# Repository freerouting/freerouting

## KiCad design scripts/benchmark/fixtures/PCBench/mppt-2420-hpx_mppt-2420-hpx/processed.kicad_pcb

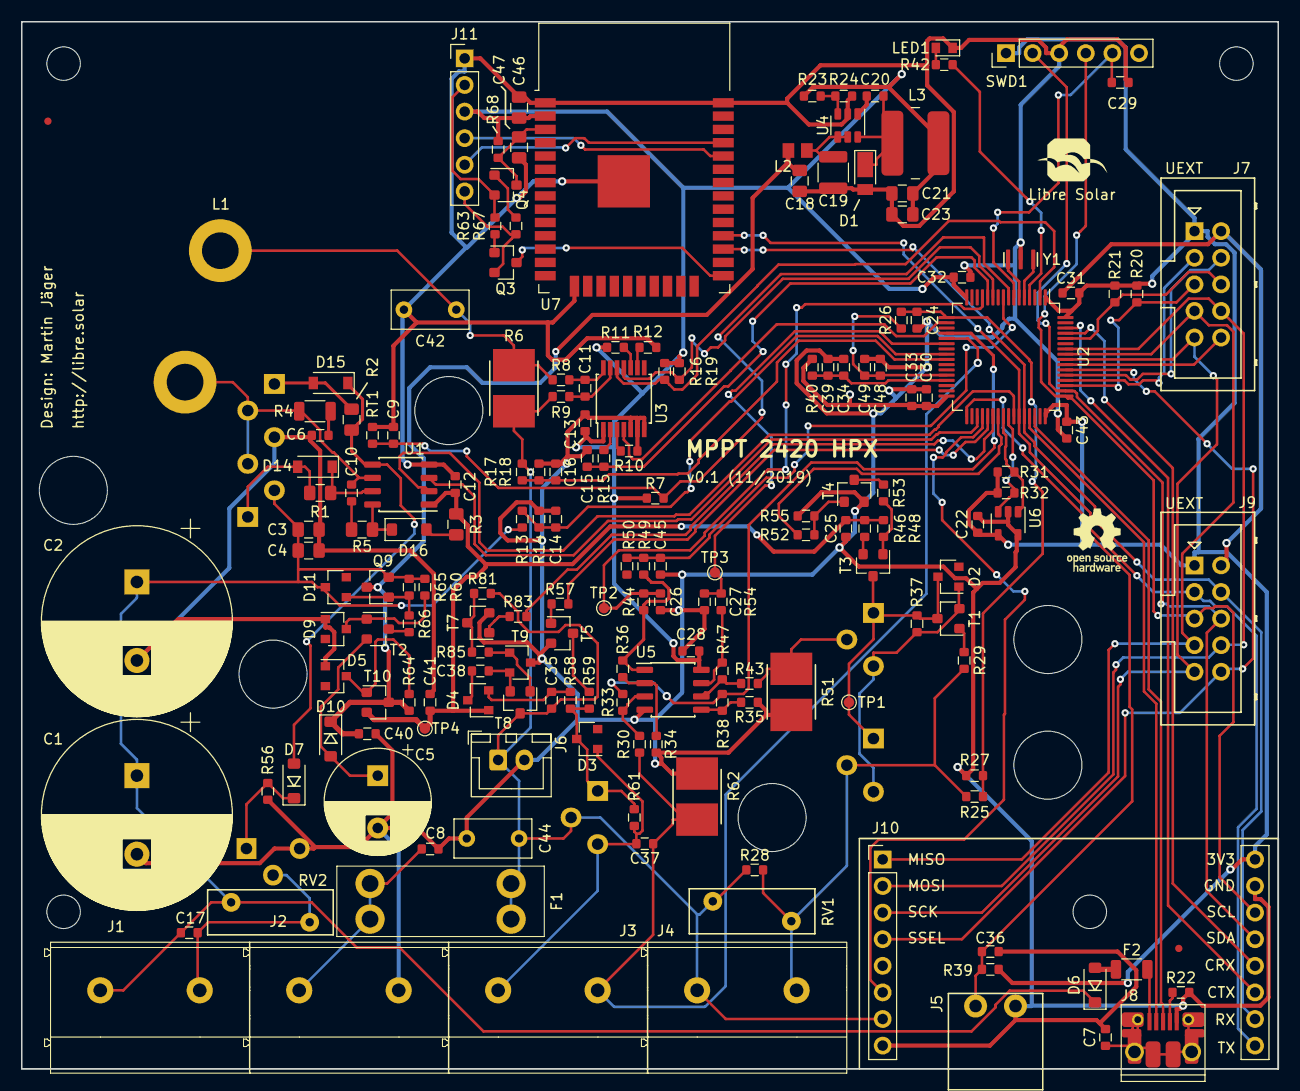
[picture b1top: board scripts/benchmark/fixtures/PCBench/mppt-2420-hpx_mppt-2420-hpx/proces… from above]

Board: 4 copper layers, 120.0 x 100.0 mm, 191 parts (0 on the bottom side), 116 nets.

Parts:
C1, C2: 560µF; CP_Radial_D18.0mm_P7.50mm
C3, C18: 1µF; C_0805_2012
C4: 100nF; C_0805_2012
C5: 820µF; CP_Radial_D10.0mm_P5.00mm
C6: 1nF; C_0603_1608
C7, C8, C14, C16, C17, C24, C26, C27, C34, C37, C38, C45: 10nF; C_0603_1608
C9, C10, C13, C15, C20, C22, C25, C28, C29, C30, C31, C32, C35, C36, C43, C48: 100nF; C_0603_1608
C11: 100pF; C_0603_1608
C12, C33, C39, C49: 2.2µF; C_0603_1608
C19: 4.7µF; C_1210_3225
C21, C23, C46: 10µF; C_0805_2012
C40: 1µF; C_0603_1608
C41: 4.7µF; C_0603_1608
C42, C44: 0.22µF; C_Rect_L7.2mm_W3.5mm_P5.00mm_FKS2_FKP2_MKS2_MKP2
C47: 2.2µF; C_0805_2012
D1: SS16FP; D_PowerDI-123
D2, D3, D5, D9, D11: 12V; D_SOT-23_ANK
D4: BAT54S; SOT-23
D6, D10, D16: 1N4148; D_SOD-123
D7, D14, D15: SS14FL; D_SOD-123
F1: 25A; Keystone-Fuse-3557-2
F2: 200mA; R_1206_3216
FID1, FID2: Fiducial; Fiducial_0.7mm
J1, J2, J3, J4: MKDS 5/ 2-9,5; Phoenix_Contact_MKDS_5-2-9,5
J5: Phoenix Contact MC 1,5; Phoenix_Contact_MC_1,5_2-G-3,81
J6: JST XH; JST_XH_B2B-XH-A_1x02_P2.50mm_Vertical
J7, J9: UEXT; Box_Header_2x05x2.54mm_Straight
J8: USB Micro B; USB_Micro-B_10103594-0001LF
J10: CommsExt_2x8
J11: Conn_01x06; PinHeader_1x06_P2.54mm_Vertical
L1: 33µH; L-FERYSTER-DTMSS-27
L2: 4.7µH; L_0805_2012Metric
L3: 47µH; Bourns_SRN6045TA
LED1: red; LED_0603_1608Metric
LOGO1: LIBRE_SOLAR; LIBRESOLAR_LOGO
LOGO2: OPEN_HARDWARE; OSHW-Logo_5.7x6mm_SilkScreen
MK1, MK2, MK3, MK4: Mounting_Hole; MountingHole_3.2mm_M3
Q1, Q2, Q5, Q6, Q7, Q8: IPA045N10N3G; TO-220-3_Horizontal_BottomHeatsink
Q3, Q4: MMBT3904; SOT-23
Q9: DMP10H4D2S; SOT-23
R1, R2, R3, R5: 3R3; R_0805_2012
R4: 2R2; R_1206_3216
R6, R51, R62: 2m; R_Bourns_CRE2512
R7, R14, R16, R19, R24, R39, R59, R63, R67, R68, R83: 10k; R_0603_1608
R8, R9: 10R; R_0603_1608
R10, R12, R15: ?; R_0603_1608
R11, R13, R17, R22, R58, R81: 100k; R_0603_1608
R18: 5.6k; R_0603_1608
R20, R21, R30, R31, R32, R34, R35, R43, R52, R54, R57: 2.2k; R_0603_1608
R23: 33k; R_0603_1608
R25, R29, R48, R53, R55: 120k; C_0603_1608
R26, R50: 8.2k; C_0603_1608
R27, R49: 12k; C_0603_1608
R28, R60, R64, R65, R66: 12k; R_0603_1608
R33, R36, R38, R47: 68k; C_0603_1608
R37: 39k; R_0603_1608
R40: 100R; R_0603_1608
R42, R46: 470R; R_0603_1608
R44: 2.2k; C_0603_1608
R56, R61: 1M; R_0603_1608
R85: 1k; R_0603_1608
RT1: 10k; R_0603_1608
RV1, RV2: 56V; RV_Disc_D12mm_W4.3mm_P7.5mm
SWD1: ST_Nucleo_SWD; PinHeader_1x06_P2.54mm_Vertical
T1, T2, T4, T5, T7, T8, T10: MMBT3904; SOT-23
T3, T9: MMBT3906; SOT-23
TEST: TestPoint_Pad_1.0x1.0mm
TP1: G_PWM; TestPoint_Pad_D1.0mm
TP2: I_LOAD; TestPoint_Pad_D1.0mm
TP3: I_SOLAR; TestPoint_Pad_D1.0mm
TP4: 12V; TestPoint_Pad_D1.0mm
U1: LM5107; SOIC-8_3.9x4.9mm_Pitch1.27mm
U2: STM32G431RBTx; LQFP-64_10x10mm_P0.5mm
U3: INA303A1; TSSOP-14_4.4x5mm_P0.65mm
U4: LMR16006X; SOT-23-6
U5: TLV9002; SOIC-8_3.9x4.9mm_Pitch1.27mm
U6: 24AA01; SOT-23-5
U7: ESP32-WROOM-32D; ESP32-WROOM-32
Y1: 8MHz; Resonator_Murata_CSTNE

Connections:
+3V3: C13.2, C21.1, C22.1, C23.1, C28.1, C30.1, C31.1, C32.1, C33.1, C43.1, C46.1, J7.1, J9.1, J10.16, J11.3, L3.2, R7.1, R11.2, R16.2, R19.2, R20.2, R21.2, R23.1, R31.2, R32.2, R39.1, R40.2, R68.2, SWD1.1, U2.1, U2.16, U2.32, U2.48, U2.64, U3.1, U5.8, U6.4, U7.2
+12V: C12.1, C25.1, C41.1, D4.1, R3.2, R46.1, R48.2, T10.2, TP4.1, U1.1
/Accessories/CAN_RX: J10.12, U2.61
/Accessories/CAN_TX: J10.11, U2.62
/Accessories/COM_I2C_SCL: J9.5, J10.14, SWD1.4, U2.49
/Accessories/COM_I2C_SDA: J9.6, J10.13, SWD1.2, U2.50
/Accessories/COM_MISO: J7.7, J9.7, J10.1, U2.57
/Accessories/COM_MOSI: J7.8, J9.8, J10.2, U2.58
/Accessories/COM_PWRI: J10.6, U2.36
/Accessories/COM_RX: J9.4, J10.10, U2.44, U7.27
/Accessories/COM_SCK: J7.9, J9.9, J10.3, U2.56
/Accessories/COM_SSEL: J9.10, J10.4, U2.54
/Accessories/COM_TX: J9.3, J10.9, U2.43, U7.28
/Accessories/DTR: J11.6, Q3.2, R67.2
/Accessories/FTDI_RX: J11.5, U7.35
/Accessories/FTDI_TX: J11.4, U7.34
/Accessories/GPIO0: Q3.3, U7.25
/Accessories/RESET: C47.1, Q4.3, R68.1, U7.3
/Accessories/RTS: J11.2, Q4.2, R63.2
/BAT+: C8.1, F1.2, J2.1
/DC/DC/HS_DRV: D14.1, R1.2, U1.7
/DC/DC/LS_DRV: D7.2, D15.1, R2.2, U1.5
/DC/DC/NOC_ALERT: R19.1, U2.11, U3.11
/DC/DC/POC_ALERT: R16.1, U2.2, U3.12
/DC/DC/PWM_HS: U1.2, U2.42
/DC/DC/PWM_LS: U1.3, U2.35
/DC/DC/SHUNT+: C42.1, L1.2, R6.2, R8.1
/DC/DC/SW_NODE: C10.2, L1.1, Q1.3, Q2.2, R4.2, U1.6
/DCDC_HV+: C1.1, C2.1, C3.1, C4.1, C17.1, D6.1, D11.1, J1.1, Q1.2, Q9.2, R13.1, R60.2, R65.2, RV2.1
/DCDC_HV-: C17.2, J1.2, Q8.2, RV2.2
/LOAD+: C37.1, D3.2, J3.1, Q7.3, R61.2
/LOAD-: C37.2, J3.2, R30.2, R62.1, U2.21
/LV switches/CP_OUT: C35.1, D4.2, R58.1
/LV switches/CP_PWM: R83.2, U2.38
/LV switches/CP_SW: C38.2, T8.2, T9.2
/LV switches/G_PWM: D2.1, Q5.1, Q6.1, R37.1, T1.3, T3.3, TP1.1
/LV switches/PWM_SW_EN: R52.2, U2.39
/LV switches/S_SHUNT-: Q6.2, R43.2, R51.1
/MCU/ADC1_IN4: C24.1, R25.2, R26.2, R27.1, U2.17
/MCU/ADC1_IN6: C9.1, R7.2, RT1.1, U2.8
/MCU/ADC1_IN12: C16.1, R17.2, R18.1, U2.25
/MCU/ADC1_IN15: C14.1, R13.2, R14.1, U2.24
/MCU/ADC2_IN5: C27.1, R54.2, TP3.1, U2.22
/MCU/ADC12_IN1: C15.1, R15.2, U2.12
/MCU/ADC12_IN2: C26.1, R44.2, TP2.1, U2.13
/MCU/COMP3_INP: C45.1, R49.1, R50.2, U2.9
/MCU/DAC1: U2.18, U3.4
/MCU/DAC2: R33.1, R38.2, U2.20
/MCU/GPIOB_15: R57.1, U2.37
/MCU/GPIOD_PD2: J7.10, U2.55
/MCU/I2C1_SCL: J7.5, R20.1, U2.51
/MCU/I2C1_SDA: J7.6, R21.1, U2.60
/MCU/I2C3_SCL: R31.1, U2.40, U6.1
/MCU/I2C3_SDA: R32.1, U2.41, U6.3
/MCU/LED_PWR: R42.2, U2.4
/MCU/OSC_IN: U2.5, Y1.3
/MCU/OSC_OUT: U2.6, Y1.1
/MCU/TEMP_BAT: C36.1, J5.1, R39.2, U2.33
/MCU/USART3_RX: J7.4, U2.53
/MCU/USART3_TX: J7.3, U2.52
/MCU/USB_DM: J8.2, U2.45
/MCU/USB_DP: J8.3, U2.46
/MCU/~RESET: C29.1, SWD1.5, U2.7
/PWM_SW-: J4.2, Q5.2, R25.1, R28.2, R29.2, RV1.2
/Power Supply/SMPS_SUPPLY: C18.1, C40.1, D10.1, L2.1, Q9.3, R64.2, T10.3
GND: C1.2, C2.2, C3.2, C4.2, C5.2, C6.2, C7.2, C8.2, C9.2, C12.2, C13.1, C14.2, C15.2, C16.2, C18.2, C19.2, C21.2, C22.2, C23.2, C24.2, C25.2, C26.2, C27.2, C28.2, C29.2, C30.2, C31.2, C32.2, C33.2, C34.2, C36.2, C39.2, C40.2, C41.2, C42.2, C43.2, C44.1, C45.2, C46.2, C47.2, C48.2, C49.2, D1.2, D5.2, D9.2, J2.2, J5.2, J6.2, J7.2, J8.5, J9.2, J10.8, J10.15, J11.1, LED1.1, Q2.3, Q8.3, R10.1, R12.1, R14.2, R18.2, R22.2, R24.2, R27.2, R34.2, R35.2, R51.2, R55.2, R56.2, R62.2, RT1.2, SWD1.3, T4.2, T5.2, T7.2, T9.3, U1.4, U3.5, U3.6, U3.7, U4.2, U5.4, U6.2, U6.5, U7.1, U7.15, U7.38, U7.39, Y1.2
unnamed: C6.1, R4.1
unnamed: C7.1, J8.6
unnamed: C10.1, R5.2
unnamed: C11.1, R8.2, U3.14
unnamed: C11.2, R9.2, U3.13
unnamed: C19.1, L2.2, U4.4, U4.5
unnamed: C20.1, U4.1
unnamed: C20.2, D1.1, L3.1, U4.6
unnamed: C38.1, D4.3
unnamed: D2.2, Q5.3, Q6.3, R37.2, T1.2
unnamed: D3.1, Q7.1, R58.2, R59.2, R61.1
unnamed: D5.1, R64.1, T10.1
unnamed: D6.2, F2.1
unnamed: D7.1, Q8.1, R56.1
unnamed: D9.1, R60.1, T2.1
unnamed: D11.2, Q9.1, R65.1, R66.2
unnamed: D14.2, Q1.1, R1.1
unnamed: D15.2, Q2.1, R2.1
unnamed: D16.1, R5.1, U1.8
unnamed: D16.2, R3.1
unnamed: F2.2, J8.1
unnamed: J8.4, R22.1
unnamed: LED1.2, R42.1
unnamed: Q3.1, R63.1
unnamed: Q4.1, R67.1
unnamed: R10.2, U3.3
unnamed: R11.1, U3.10
unnamed: R12.2, U3.9
unnamed: R15.1, U3.2
unnamed: R23.2, R24.1, U4.3
unnamed: R29.1, T1.1
unnamed: R30.1, R33.2, U5.3
unnamed: R34.1, R36.1, U5.2
unnamed: R35.1, R38.1, U5.5
unnamed: R36.2, R44.1, R49.2, U5.1
unnamed: R43.1, R47.1, U5.6
unnamed: R46.2, T3.2
unnamed: R47.2, R54.1, U5.7
unnamed: R48.1, R53.2, T3.1
unnamed: R52.1, R55.1, T4.1
unnamed: R53.1, T4.3
unnamed: R57.2, T5.1
unnamed: R59.1, T5.3
unnamed: R66.1, T2.3
unnamed: R81.1, R85.1, T7.3
unnamed: R83.1, T7.1
unnamed: R85.2, T8.1, T9.1
VBUS: C5.1, C35.2, C44.2, D10.2, F1.1, J4.1, J6.1, J10.7, Q7.2, R6.1, R9.1, R17.1, R28.1, R81.2, RV1.1, T2.2, T8.3
VDDA: C34.1, C39.1, R40.1, U2.29
VREF: C48.1, C49.1, R26.1, U2.28

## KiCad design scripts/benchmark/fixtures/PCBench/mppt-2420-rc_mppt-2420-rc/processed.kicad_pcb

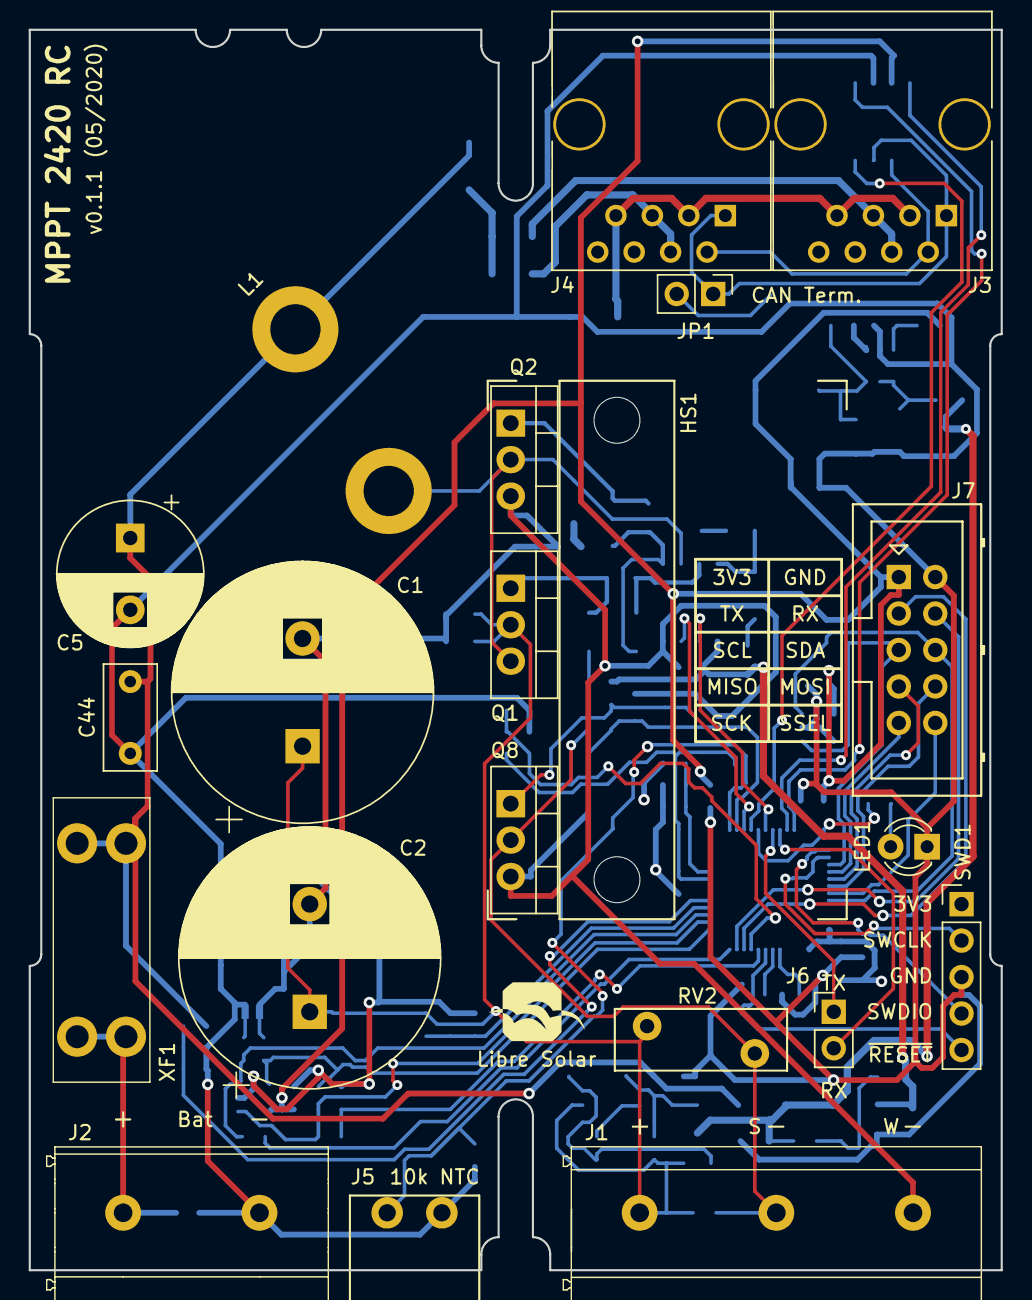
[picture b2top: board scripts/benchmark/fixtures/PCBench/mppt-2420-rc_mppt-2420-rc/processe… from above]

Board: 4 copper layers, 67.7 x 86.4 mm, 120 parts (0 on the bottom side), 71 nets.

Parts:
C1, C2: 560µF; CP_Radial_D18.0mm_P7.50mm
C3, C18, C40: 1µF; C_0805_2012
C4: 100nF; C_0805_2012
C5: 820µF; CP_Radial_D10.0mm_P5.00mm
C6, C15: 1nF; C_0603_1608
C7, C9, C10, C11, C20, C22, C29, C30, C31, C32, C36, C48: 100nF; C_0603_1608
C8, C14, C16, C17, C34: 10nF; C_0603_1608
C12, C33, C39, C41, C49: 2.2µF; C_0603_1608
C19: 4.7µF; C_1210_3225
C21, C23: 10µF; C_0805_2012
C44: 0.22µF; C_Rect_L7.2mm_W3.5mm_P5.00mm_FKS2_FKP2_MKS2_MKP2
D1: SS16FP; D_PowerDI-123
D2, D3: NRVTS260ESFT1G; D_SOD-123
D5, D9, D11: 12V; D_SOT-23_ANK
D7, D14, D15: SS14FL; D_SOD-123
D8: 2.5V; D_SOD-123
D10, D16: 1N4148; D_SOD-123
F1: 25A; NULL
F2, F3: 600mA; Fuse_1206_3216Metric
FID1, FID2: Fiducial; Fiducial_0.7mm
HS1: Heatsink; Fischer_Elektronik_SK573_37,5
J1: MKDS 5/ 3-9,5; Phoenix_Contact_MKDS_5-3-9,5
J2: MKDS 5/ 2-9,5; Phoenix_Contact_MKDS_5-2-9,5
J3, J4: 8P8C; RJ45_8P8C
J5: Phoenix Contact MC 1,5; Phoenix_Contact_MC_1,5_2-G-3,81
J6: Conn_01x02; PinHeader_1x02_P2.54mm_Vertical
J7: UEXT; Box_Header_2x05x2.54mm_Straight
JP1: Jumper_NC_Small; PinHeader_1x02_P2.54mm_Vertical
L1: 33µH; L-FERYSTER-DTMSS-27
L2: 4.7µH; L_0805_2012Metric
L3: 47µH; Bourns_SRN6045TA
LED1: red; LED_D3.0mm
LOGO1: LIBRE_SOLAR; LIBRESOLAR_LOGO
LOGO2: OPEN_HARDWARE; OSHW-Logo_5.7x6mm_SilkScreen
NT1, NT2: Net-Tie_2; NetTie-2_SMD_Pad0.5mm
Q1, Q2, Q8: IPP045N10N3G; TO-220-3_Vertical
Q9: DMP10H4D2S; SOT-23
R1, R2, R3, R5: 3R3; R_0805_2012
R4: 2R2; R_1206_3216
R6: 2m; R_Bourns_CRE2512
R7, R24, R39, R41, R45, R64, R65, R66: 10k; R_0603_1608
R8, R10, R14, R20, R21: 2.2k; R_0603_1608
R9, R11: 68k; R_0603_1608
R12: 0R; R_0603_1608
R13, R17: 100k; R_0603_1608
R15, R42: 1k; R_0603_1608
R18: 5.6k; R_0603_1608
R22: 120R; R_1206_3216
R23, R60: 33k; R_0603_1608
R40: 100R; R_0603_1608
R56: 1M; R_0603_1608
RT1: 10k; R_0603_1608
RV2: 82V; RV_Disc_D12mm_W4.3mm_P7.5mm
SWD1: ST_Nucleo_SWD; PinHeader_1x05_P2.54mm_Vertical
T2, T6, T10: MMBT3904; SOT-23
TP4: 12V; TestPoint_Pad_D1.0mm
U1: LM5107; SOIC-8_3.9x4.9mm_Pitch1.27mm
U2: STM32G431CBTx; LQFP-48_7x7mm_P0.5mm
U3: TLV9001; SOT-23-5
U4: LMR16006X; SOT-23-6
U5: TCAN334; SOIC-8_3.9x4.9mm_Pitch1.27mm
U6: 24AA32; SOT-23-5
XF1: ATO blade fuse; Keystone-Fuse-3557-2
Y1: 8MHz; Resonator_Murata_CSTNE

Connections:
+3V3: C7.1, C11.1, C21.1, C22.1, C23.1, C30.1, C31.1, C32.1, C33.1, J7.1, L3.2, R20.2, R21.2, R23.1, R40.2, SWD1.1, U2.1, U2.48, U3.5, U5.3, U6.4
+12V: C12.1, C41.1, R3.2, R12.1, T10.2, TP4.1, U1.1
/BAT+: C8.1, J2.1, XF1.2
/CAN bus/CAN_GND: D3.2, J3.3, J3.7, J4.3, J4.7
/CAN bus/CAN_H: J3.1, J4.1, JP1.1, U5.7
/CAN bus/CAN_L: J3.2, J4.2, R22.2, U5.6
/CAN bus/CAN_RX: U2.33, U5.4
/CAN bus/CAN_STB: U2.28, U5.8
/CAN bus/CAN_TX: U2.34, U5.1
/CAN bus/CAN_V+1: F2.1, J3.4, J3.5
/CAN bus/CAN_V+2: F3.1, J4.4, J4.5
/DC/DC/HS_DRV: D14.1, R1.2, U1.7
/DC/DC/LS_DRV: D7.2, D15.1, R2.2, U1.5
/DC/DC/PWM_HS: U1.2, U2.30
/DC/DC/PWM_LS: U1.3, U2.27
/DC/DC/SHUNT_N: NT1.2, R10.1
/DC/DC/SHUNT_P: NT2.2, R8.1
/DC/DC/SW_NODE: C10.2, L1.1, Q1.3, Q2.2, R4.2, U1.6
/DCDC_HV+: C1.1, C2.1, C3.1, C4.1, C17.1, D11.1, J1.1, Q1.2, Q9.2, R13.1, R60.2, R65.2, RV2.1
/DCDC_HV-: C17.2, J1.2, Q8.2, R41.1, RV2.2
/MCU/ADC1_IN2: C9.1, R7.2, RT1.1, U2.9
/MCU/ADC1_IN11: D8.1, R41.2, T6.1, U2.26
/MCU/ADC1_IN12: C16.1, R17.2, R18.1, U2.17
/MCU/ADC1_IN15: C14.1, R13.2, R14.1, U2.16
/MCU/ADC2_IN1: C15.1, R15.2, U2.8
/MCU/DAC1: R9.1, U2.12
/MCU/I2C1_SCL: J7.5, R20.1, U2.39, U6.1
/MCU/I2C1_SDA: J7.6, R21.1, U2.44, U6.3
/MCU/LED_PWR: R42.2, U2.29
/MCU/OPAMP2_VINM: R10.2, R11.1, U2.13, U3.4
/MCU/OPAMP2_VINP: R8.2, R9.2, U2.15, U3.3
/MCU/OPAMP2_VOUT: R11.2, R15.1, U2.14, U3.1
/MCU/OSC_IN: U2.5, Y1.3
/MCU/OSC_OUT: U2.6, Y1.1
/MCU/SPI1_MISO: J7.7, U2.41
/MCU/SPI1_MOSI: J7.8, U2.42
/MCU/SPI1_SCK: J7.9, U2.40
/MCU/SPI1_SSEL: J7.10, U2.43
/MCU/SWCLK: SWD1.2, U2.38
/MCU/SWDIO: SWD1.4, U2.37
/MCU/TEMP_BAT: C36.1, J5.1, R39.2, U2.25
/MCU/USART1_RX: J6.2, U2.32
/MCU/USART1_TX: J6.1, U2.31
/MCU/USART2_RX: J7.4, U2.11
/MCU/USART2_TX: J7.3, U2.10
/MCU/~RESET: C29.1, SWD1.5, U2.7
/Power Supply/SMPS_SUPPLY: C18.1, C40.1, D10.1, L2.1, Q9.3, R64.2, T10.3
GND: C5.2, C7.2, C8.2, C9.2, C11.2, C14.2, C15.2, C16.2, C18.2, C19.2, C21.2, C22.2, C23.2, C29.2, C30.2, C31.2, C32.2, C33.2, C34.2, C36.2, C39.2, C40.2, C41.2, C44.1, C48.2, C49.2, D1.2, D3.1, D5.2, D9.2, J2.2, J5.2, J7.2, LED1.1, NT2.1, R6.1, R14.2, R18.2, R24.2, RT1.2, SWD1.3, U3.2, U4.2, U5.2, U6.2, U6.5, Y1.2
GNDPWR: C1.2, C2.2, C3.2, C4.2, C6.2, C12.2, D8.2, J1.3, NT1.1, Q2.3, Q8.3, R6.2, R56.2, T6.2, U1.4
unnamed: C6.1, R4.1
unnamed: C10.1, R5.2
unnamed: C19.1, L2.2, U4.4, U4.5
unnamed: C20.1, U4.1
unnamed: C20.2, D1.1, L3.1, U4.6
unnamed: D2.1, F2.2, F3.2
unnamed: D5.1, R64.1, T10.1
unnamed: D7.1, R12.2, R45.1
unnamed: D9.1, R60.1, T2.1
unnamed: D11.2, Q9.1, R65.1, R66.2
unnamed: D14.2, Q1.1, R1.1
unnamed: D15.2, Q2.1, R2.1
unnamed: D16.1, R5.1, U1.8
unnamed: D16.2, R3.1
unnamed: JP1.2, R22.1
unnamed: LED1.2, R42.1
unnamed: Q8.1, R45.2, R56.1, T6.3
unnamed: R23.2, R24.1, U4.3
unnamed: R66.1, T2.3
VBUS: C5.1, C44.2, D2.2, D10.2, L1.2, R17.1, T2.2, XF1.1
VDDA: C34.1, C39.1, R40.1, U2.21
VREF: C48.1, C49.1, R7.1, R39.1, U2.20

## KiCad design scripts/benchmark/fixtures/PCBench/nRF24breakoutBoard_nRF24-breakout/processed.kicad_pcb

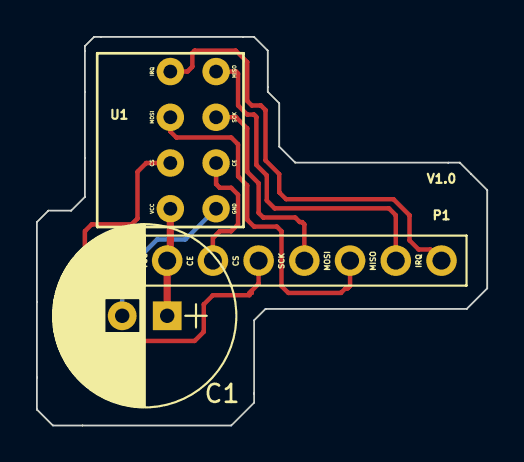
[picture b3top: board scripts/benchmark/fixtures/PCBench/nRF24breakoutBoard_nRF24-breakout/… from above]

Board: 2 copper layers, 25.0 x 21.6 mm, 3 parts (0 on the bottom side), 8 nets.

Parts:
C1: 10uF; CP_Radial_D10.0mm_P2.50mm
P1: CONN_01X08; Pin_Header_Straight_1x08_Pitch2.54mm
U1: nRF24

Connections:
unnamed: C1.1, P1.2, U1.2
unnamed: C1.2, P1.1, U1.1
unnamed: P1.3, U1.3
unnamed: P1.4, U1.4
unnamed: P1.5, U1.5
unnamed: P1.6, U1.6
unnamed: P1.7, U1.7
unnamed: P1.8, U1.8
